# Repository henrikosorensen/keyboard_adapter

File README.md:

# keyboard_adapter
Simple Arduino ProMicro hat to turn it into a ADB or PS/2 keyboard to USB adapter

Flash your promicro with [TMK ADB_USB](https://github.com/tmk/tmk_keyboard/tree/master/converter/adb_usb), [TMK PS2_USB](https://github.com/tmk/tmk_keyboard/tree/master/converter/ps2_usb) or [Soarer's converter firmware](https://geekhack.org/index.php?topic=17458.0)

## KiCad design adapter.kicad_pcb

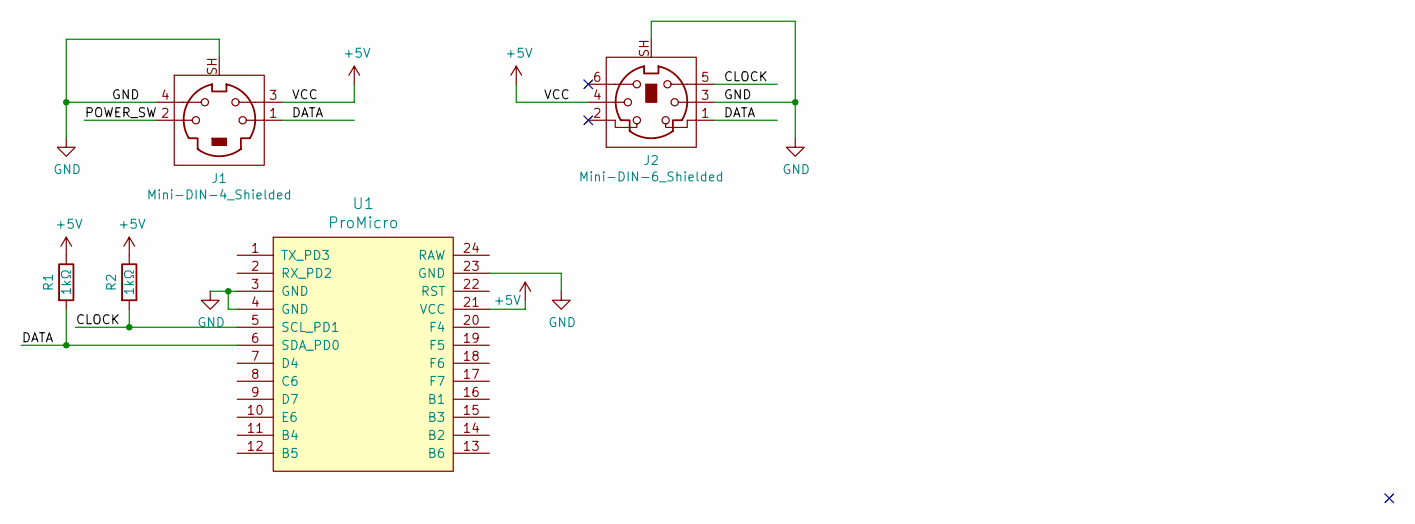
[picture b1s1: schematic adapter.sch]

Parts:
J1: Mini-DIN-4_Shielded; Mini-Din-4_CUI_MD-40FC
J2: Mini-DIN-6_Shielded; Mini-Din-6_CUI_MD-60FC
R1, R2: 1kΩ; R_1206_3216Metric_Pad1.42x1.75mm_HandSolder
U1: ProMicro

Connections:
+5V: J1.3, J2.4, R1.1, R2.1, U1.21 (VCC)
/CLOCK: J2.5, R2.2, U1.5 (SCL_PD1)
/DATA: J1.1, J2.1, R1.2, U1.6 (SDA_PD0)
/POWER_SW: J1.2
GND: J1.4, J1.SH, J2.3, J2.SH, U1.3 (GND), U1.4 (GND), U1.23 (GND)

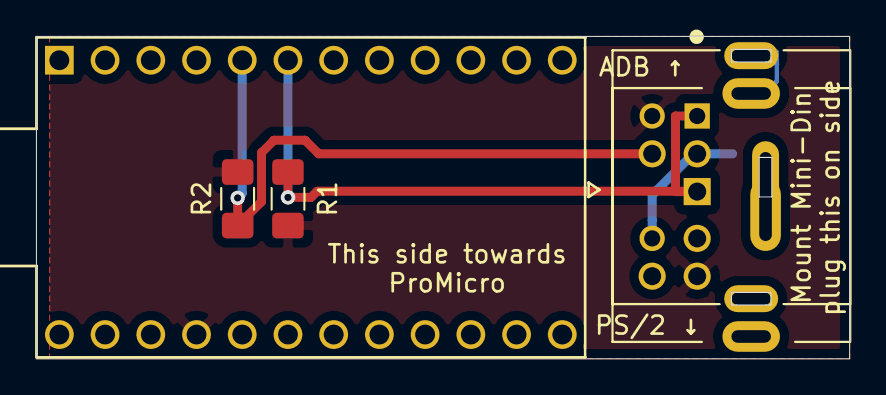
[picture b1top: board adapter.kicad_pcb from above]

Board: 2 copper layers, 45.2 x 17.9 mm, 5 parts (1 on the bottom side), 4 nets.

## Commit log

2019-04-08 import
